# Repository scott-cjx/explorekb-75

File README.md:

# explorekb-75
an open source 75% layout keyboard project as a start to my exploration in my keyboard making journey.

## Changelog

<ul>

<li>
Rev 4

Due to conflict of space between Controller Board and plate, controller board is shifted, allowing for plate to cover full length of Keyboard PCB.

Keyboard PCB:
- Shifted Blackpill Controller Board to the edge of the keyboard PCB, cut-out Keyboard PCB to allow for Blackpill to solder directly onto keyboard PCB with the USB port be like a center-mount USB on the keyboard PCB.
- Rotated OLED display 180 degrees. (now facing down)

Plate:

- WIP

</li>

<li>
Rev 3 

Keyboard PCB:
- Reverted back to using development board as controller, specifically using WeAct Studio Blackpill STM32F401 Controller Board.
- Tweaked layout to have 15 keys on ROW 0, including last 2 columns, COL 13 and 14 to be EC11 rotary encoders.
- Changed to have all diodes be BAT54C.
- Added OLED screen. (facing up)

Plate: <br>
Due to conflict of space between Controller Board and plate, the plate is unable to cover full length of Keyboard PCB, 3d printing the plate is then the safer option.

- Due to the change in layout from Rev 2 to Rev 3, <b> Rev 2 plates are NOT compatible with Rev 3 Keyboard PCB</b>.

</li>

<li>
Rev 2

Keyboard PCB:

Plate:

</li>

</ul>

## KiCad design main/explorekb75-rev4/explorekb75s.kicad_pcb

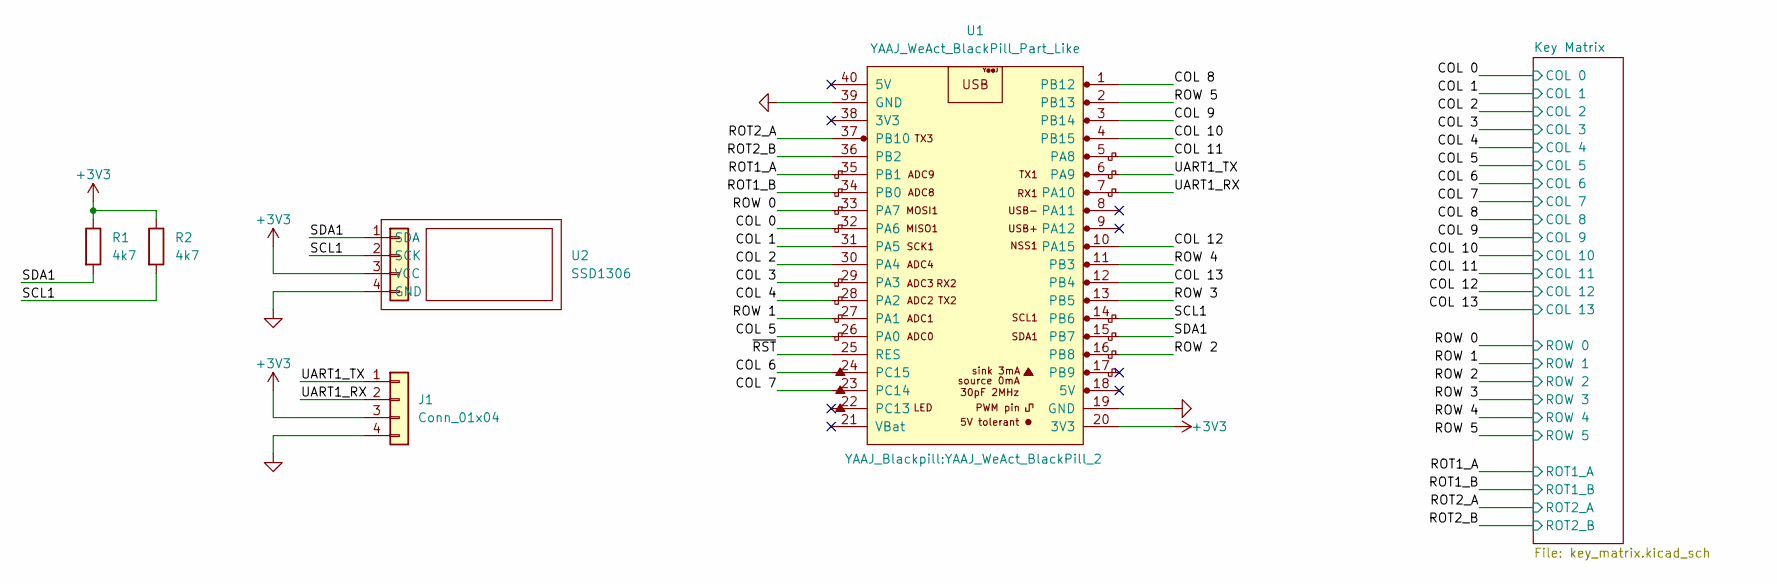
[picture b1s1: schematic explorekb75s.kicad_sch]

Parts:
J1: Conn_01x04
R1, R2: 4k7; C_0603_1608Metric_Pad1.08x0.95mm_HandSolder
U1: YAAJ_WeAct_BlackPill_Part_Like; YAAJ_WeAct_BlackPill_2
U2: SSD1306; SSD1306_128X32

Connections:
+3V3: J1.3, R1.1, R2.1, U1.20 (3V3), U2.3 (VCC)
/COL 0: U1.32 (PA6); also elsewhere on the board
/COL 1: U1.31 (PA5); also elsewhere on the board
/COL 2: U1.30 (PA4); also elsewhere on the board
/COL 3: U1.29 (PA3); also elsewhere on the board
/COL 4: U1.28 (PA2); also elsewhere on the board
/COL 5: U1.26 (PA0); also elsewhere on the board
/COL 6: U1.24 (PC15); also elsewhere on the board
/COL 7: U1.23 (PC14); also elsewhere on the board
/COL 8: U1.1 (PB12); also elsewhere on the board
/COL 9: U1.3 (PB14); also elsewhere on the board
/COL 10: U1.4 (PB15); also elsewhere on the board
/COL 11: U1.5 (PA8); also elsewhere on the board
/COL 12: U1.10 (PA15); also elsewhere on the board
/COL 13: U1.12 (PB4); also elsewhere on the board
/ROT1_A: U1.35 (PB1); also elsewhere on the board
/ROT1_B: U1.34 (PB0); also elsewhere on the board
/ROT2_A: U1.37 (PB10); also elsewhere on the board
/ROT2_B: U1.36 (PB2); also elsewhere on the board
/ROW 0: U1.33 (PA7); also elsewhere on the board
/ROW 1: U1.27 (PA1); also elsewhere on the board
/ROW 2: U1.16 (PB8); also elsewhere on the board
/ROW 3: U1.13 (PB5); also elsewhere on the board
/ROW 4: U1.11 (PB3); also elsewhere on the board
/ROW 5: U1.2 (PB13); also elsewhere on the board
/SCL1: R2.2, U1.14 (PB6), U2.2 (SCK)
/SDA1: R1.2, U1.15 (PB7), U2.1 (SDA)
/UART1_RX: J1.2, U1.7 (PA10)
/UART1_TX: J1.1, U1.6 (PA9)
/~RST: U1.25 (RES)
GND: J1.4, U1.19 (GND), U1.39 (GND), U2.4 (GND); also elsewhere on the board

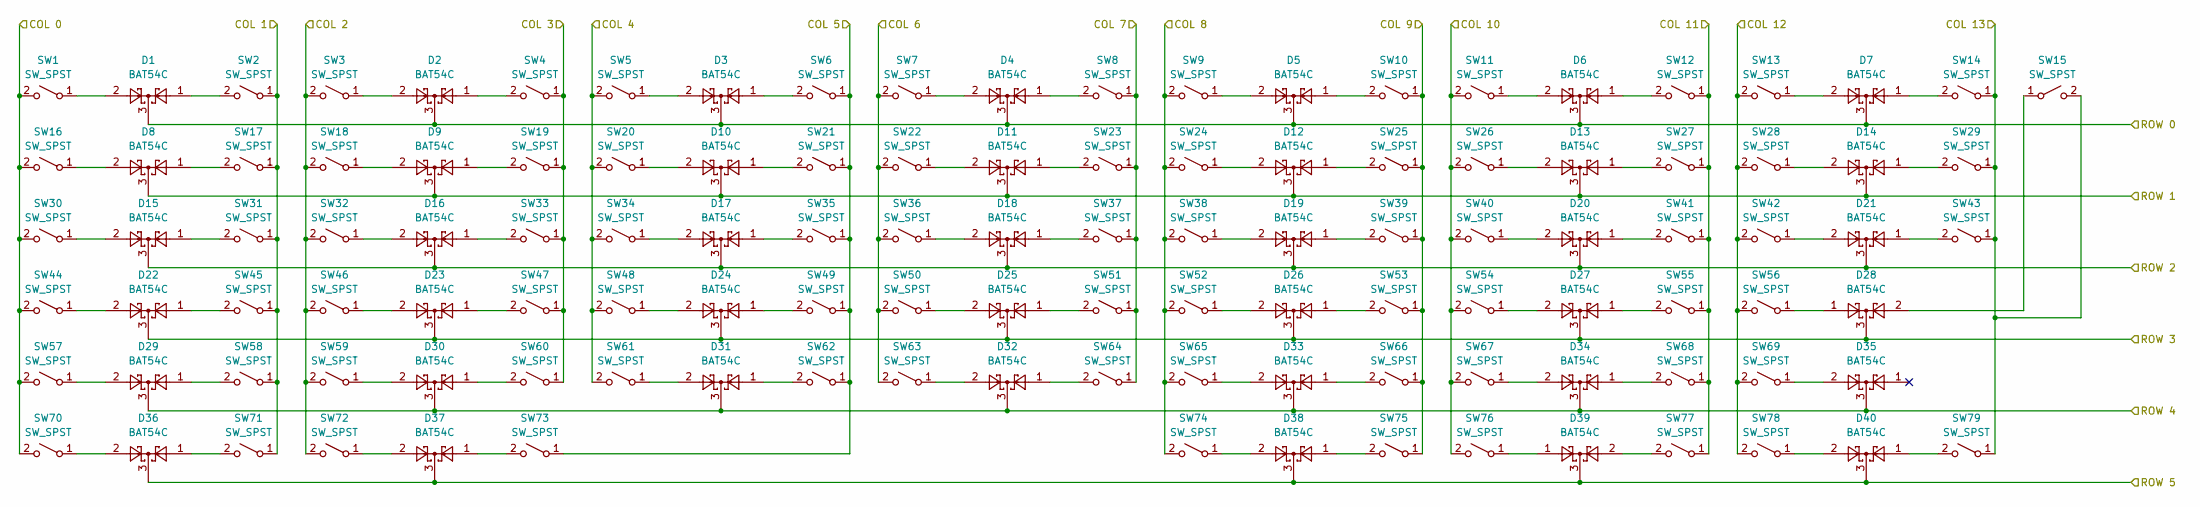
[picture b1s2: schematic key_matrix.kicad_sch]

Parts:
D1, D2, D3, D4, D5, D6, D7, D8, D9, D10, D11, D12, D13, D14, D15, D16, D17, D18, D19, D20, D21, D22, D23, D24, D25, D26, D27, D28, D29, D30, D31, D32, D33, D34, D35, D36, D37, D38, D39, D40: BAT54C; SOT-23
SW1, SW2, SW3, SW4, SW5, SW6, SW7, SW8, SW9, SW10, SW11, SW12, SW13, SW14, SW15, SW16, SW17, SW18, SW19, SW20, SW21, SW22, SW23, SW24, SW25, SW26, SW27, SW28, SW29, SW30, SW31, SW32, SW33, SW34, SW35, SW36, SW37, SW38, SW39, SW40, SW41, SW42, SW43, SW44, SW45, SW46, SW47, SW48, SW49, SW50, SW51, SW52, SW53, SW54, SW55, SW56, SW57, SW58, SW59, SW60, SW61, SW62, SW63, SW64, SW65, SW66, SW67, SW68, SW69, SW70, SW71, SW72, SW73, SW74, SW75, SW76, SW77, SW78, SW79: SW_SPST; Kailh_socket_MX

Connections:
/COL 0: SW1.2 (B), SW16.2 (B), SW30.2 (B), SW44.2 (B), SW57.2 (B), SW70.2 (B); also elsewhere on the board
/COL 1: SW2.1 (A), SW17.1 (A), SW31.1 (A), SW45.1 (A), SW58.1 (A), SW71.1 (A); also elsewhere on the board
/COL 2: SW3.2 (B), SW18.2 (B), SW32.2 (B), SW46.2 (B), SW59.2 (B), SW72.2 (B); also elsewhere on the board
/COL 3: SW4.1 (A), SW19.1 (A), SW33.1 (A), SW47.1 (A), SW60.1 (A); also elsewhere on the board
/COL 4: SW5.2 (B), SW20.2 (B), SW34.2 (B), SW48.2 (B), SW61.2 (B); also elsewhere on the board
/COL 5: SW6.1 (A), SW21.1 (A), SW35.1 (A), SW49.1 (A), SW62.1 (A), SW73.1 (A); also elsewhere on the board
/COL 6: SW7.2 (B), SW22.2 (B), SW36.2 (B), SW50.2 (B), SW63.2 (B); also elsewhere on the board
/COL 7: SW8.1 (A), SW23.1 (A), SW37.1 (A), SW51.1 (A), SW64.1 (A); also elsewhere on the board
/COL 8: SW9.2 (B), SW24.2 (B), SW38.2 (B), SW52.2 (B), SW65.2 (B), SW74.2 (B); also elsewhere on the board
/COL 9: SW10.1 (A), SW25.1 (A), SW39.1 (A), SW53.1 (A), SW66.1 (A), SW75.1 (A); also elsewhere on the board
/COL 10: SW11.2 (B), SW26.2 (B), SW40.2 (B), SW54.2 (B), SW67.2 (B), SW76.2 (B); also elsewhere on the board
/COL 11: SW12.1 (A), SW27.1 (A), SW41.1 (A), SW55.1 (A), SW68.1 (A), SW77.1 (A); also elsewhere on the board
/COL 12: SW13.2 (B), SW28.2 (B), SW42.2 (B), SW56.2 (B), SW69.2 (B), SW78.2 (B); also elsewhere on the board
/COL 13: SW14.1 (A), SW14.S2, SW15.2 (B), SW15.S1, SW29.1 (A), SW43.1 (A), SW79.1 (A); also elsewhere on the board
/Key Matrix/ROT1_2: D7.1, SW14.2 (B), SW14.S1
/Key Matrix/ROT2_2: D28.2, SW15.1 (A), SW15.S2
/ROT1_A: SW14.B; also elsewhere on the board
/ROT1_B: SW14.A; also elsewhere on the board
/ROT2_A: SW15.B; also elsewhere on the board
/ROT2_B: SW15.A; also elsewhere on the board
/ROW 0: D1.3, D2.3, D3.3, D4.3, D5.3, D6.3, D7.3; also elsewhere on the board
/ROW 1: D8.3, D9.3, D10.3, D11.3, D12.3, D13.3, D14.3; also elsewhere on the board
/ROW 2: D15.3, D16.3, D17.3, D18.3, D19.3, D20.3, D21.3; also elsewhere on the board
/ROW 3: D22.3, D23.3, D24.3, D25.3, D26.3, D27.3, D28.3; also elsewhere on the board
/ROW 4: D29.3, D30.3, D31.3, D32.3, D33.3, D34.3, D35.3; also elsewhere on the board
/ROW 5: D36.3, D37.3, D38.3, D39.3, D40.3; also elsewhere on the board
GND: SW14.C, SW15.C; also elsewhere on the board
unnamed: D1.1, SW2.2 (B)
unnamed: D1.2, SW1.1 (A)
unnamed: D2.1, SW4.2 (B)
unnamed: D2.2, SW3.1 (A)
unnamed: D3.1, SW6.2 (B)
unnamed: D3.2, SW5.1 (A)
unnamed: D4.1, SW8.2 (B)
unnamed: D4.2, SW7.1 (A)
unnamed: D5.1, SW10.2 (B)
unnamed: D5.2, SW9.1 (A)
unnamed: D6.1, SW12.2 (B)
unnamed: D6.2, SW11.1 (A)
unnamed: D7.2, SW13.1 (A)
unnamed: D8.1, SW17.2 (B)
unnamed: D8.2, SW16.1 (A)
unnamed: D9.1, SW19.2 (B)
unnamed: D9.2, SW18.1 (A)
unnamed: D10.1, SW21.2 (B)
unnamed: D10.2, SW20.1 (A)
unnamed: D11.1, SW23.2 (B)
unnamed: D11.2, SW22.1 (A)
unnamed: D12.1, SW25.2 (B)
unnamed: D12.2, SW24.1 (A)
unnamed: D13.1, SW27.2 (B)
unnamed: D13.2, SW26.1 (A)
unnamed: D14.1, SW29.2 (B)
unnamed: D14.2, SW28.1 (A)
unnamed: D15.1, SW31.2 (B)
unnamed: D15.2, SW30.1 (A)
unnamed: D16.1, SW33.2 (B)
unnamed: D16.2, SW32.1 (A)
unnamed: D17.1, SW35.2 (B)
unnamed: D17.2, SW34.1 (A)
unnamed: D18.1, SW37.2 (B)
unnamed: D18.2, SW36.1 (A)
unnamed: D19.1, SW39.2 (B)
unnamed: D19.2, SW38.1 (A)
unnamed: D20.1, SW41.2 (B)
unnamed: D20.2, SW40.1 (A)
unnamed: D21.1, SW43.2 (B)
unnamed: D21.2, SW42.1 (A)
unnamed: D22.1, SW45.2 (B)
unnamed: D22.2, SW44.1 (A)
unnamed: D23.1, SW47.2 (B)
unnamed: D23.2, SW46.1 (A)
unnamed: D24.1, SW49.2 (B)
unnamed: D24.2, SW48.1 (A)
unnamed: D25.1, SW51.2 (B)
unnamed: D25.2, SW50.1 (A)
unnamed: D26.1, SW53.2 (B)
unnamed: D26.2, SW52.1 (A)
unnamed: D27.1, SW55.2 (B)
unnamed: D27.2, SW54.1 (A)
unnamed: D28.1, SW56.1 (A)
unnamed: D29.1, SW58.2 (B)
unnamed: D29.2, SW57.1 (A)
unnamed: D30.1, SW60.2 (B)
unnamed: D30.2, SW59.1 (A)
unnamed: D31.1, SW62.2 (B)
unnamed: D31.2, SW61.1 (A)
unnamed: D32.1, SW64.2 (B)
unnamed: D32.2, SW63.1 (A)
unnamed: D33.1, SW66.2 (B)
unnamed: D33.2, SW65.1 (A)
unnamed: D34.1, SW68.2 (B)
unnamed: D34.2, SW67.1 (A)
unnamed: D36.1, SW71.2 (B)
unnamed: D36.2, SW70.1 (A)
unnamed: D37.1, SW73.2 (B)
unnamed: D37.2, SW72.1 (A)
unnamed: D38.1, SW75.2 (B)
unnamed: D38.2, SW74.1 (A)
unnamed: D39.1, SW76.1 (A)
unnamed: D39.2, SW77.2 (B)
unnamed: D40.1, SW79.2 (B)
unnamed: D40.2, SW78.1 (A)

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
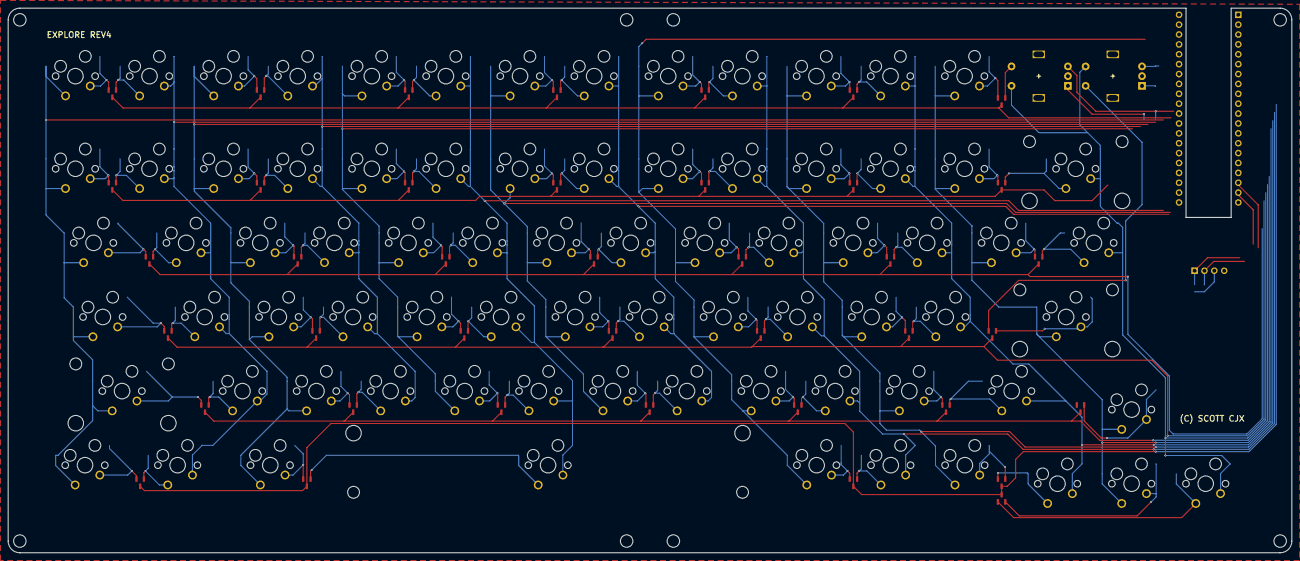
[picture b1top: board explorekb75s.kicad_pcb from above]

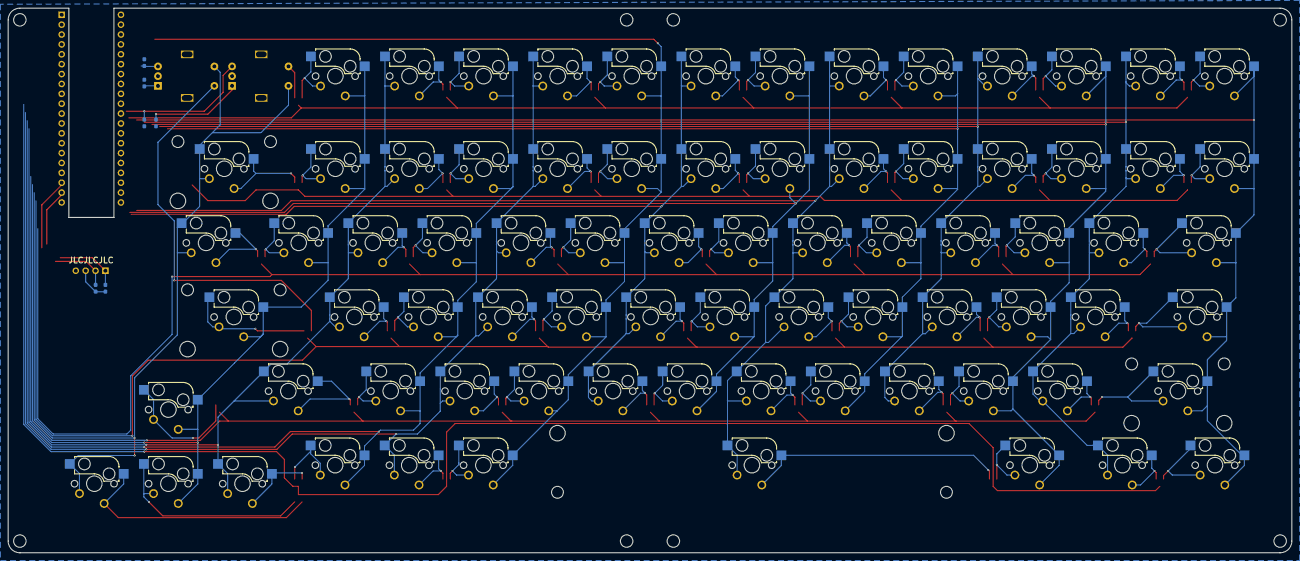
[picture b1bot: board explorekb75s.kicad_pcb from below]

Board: 2 copper layers, 330.0 x 140.0 mm, 131 parts (7 on the bottom side), 107 nets.

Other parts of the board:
C1, C2, C3, C4: 100n; C_0603_1608Metric_Pad1.08x0.95mm_HandSolder
STAB1, STAB2, STAB3: Stabilizer_MX_2u
STAB4: Stabilizer_Cherry_MX_6.25u

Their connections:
/ROT1_A: C1.1; also elsewhere on the board
/ROT1_B: C2.1; also elsewhere on the board
/ROT2_A: C3.1; also elsewhere on the board
/ROT2_B: C4.1; also elsewhere on the board
GND: C1.2, C2.2, C3.2, C4.2; also elsewhere on the board

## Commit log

2023-02-25 added v1-square-edge
2023-03-14 added init board and pcb
2023-04-29 added rev 4
2023-04-29 complete wiring for rev 4
2023-05-01 added rev3 plate v1
2023-05-01 refactored file structure
2023-05-01 modified rev 4 design
2023-05-01 refactored paths
2023-05-01 migrated rev4 to use local libraries
2023-05-01 use new kicad parts
2023-05-01 updated rev4 pcb
2023-05-02 added rev4 renders
2023-05-02 added renders for rev4
2023-05-02 modifed renders for rev4
2023-05-25 added stl for rev3 plate-v1
2023-09-29 updated files
